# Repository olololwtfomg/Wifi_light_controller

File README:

Wireless sensor nodes used for simple communication protocol testing

Hardware:
RFM70 communication module
ATmega8L
DS18B20 one wire temperature sensor (for the hell of it)
generic 3.3-2.7V low drop voltage regulator

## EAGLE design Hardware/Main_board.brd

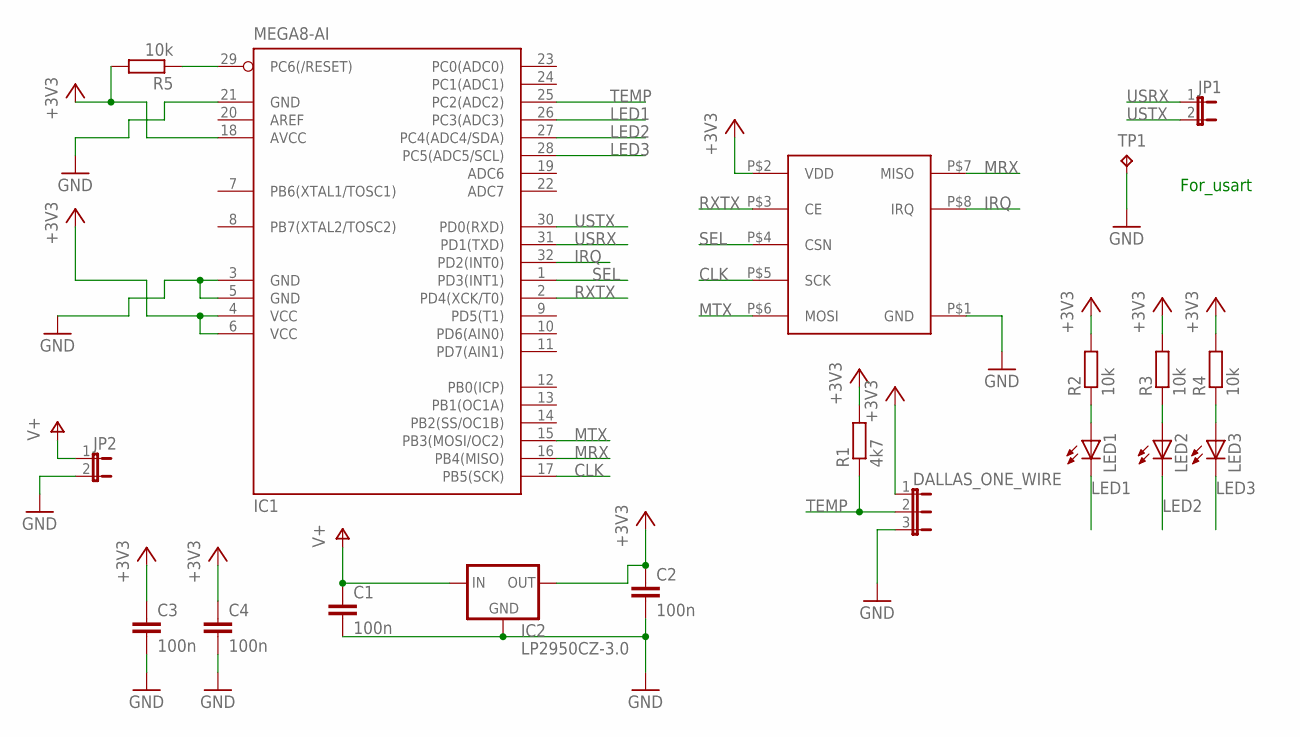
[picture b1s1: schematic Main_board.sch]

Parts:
C1, C2, C3, C4: 100n; C1206
DALLAS_ONE_WIRE: JP2E; JP2
IC1: MEGA8-AI; TQFP32-08
IC2: LP2950CZ-3.0; TO92
JP1, JP2: JP1E; JP1
LED1, LED2, LED3: LEDSMT1206; 1206
R1: 4k7; M1206
R2, R3, R4, R5: 10k; M1206
TP1: TPB2,54; B2,54
U$1: RFM70D

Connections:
+3V3: C2.1, C3.1, C4.1, DALLAS_ONE_WIRE.1, IC1.4 (VCC), IC1.6 (VCC), IC1.18 (AVCC), IC2.1 (OUT), R1.2, R2.2, R3.2, R4.2, R5.2, U$1.P$2 (VDD)
CLK: IC1.17 (PB5(SCK)), U$1.P$5 (SCK)
GND: C1.2, C2.2, C3.2, C4.2, DALLAS_ONE_WIRE.3, IC1.3 (GND), IC1.5 (GND), IC1.21 (GND), IC2.2 (GND), JP2.2, TP1.TP, U$1.P$1 (GND)
IRQ: IC1.32 (PD2(INT0)), U$1.P$8 (IRQ)
LED1: IC1.26 (PC3(ADC3)), LED1.C
LED2: IC1.27 (PC4(ADC4/SDA)), LED2.C
LED3: IC1.28 (PC5(ADC5/SCL)), LED3.C
MRX: IC1.16 (PB4(MISO)), U$1.P$7 (MISO)
MTX: IC1.15 (PB3(MOSI/OC2)), U$1.P$6 (MOSI)
unnamed: LED1.A, R2.1
unnamed: LED2.A, R3.1
unnamed: LED3.A, R4.1
unnamed: IC1.29 (PC6(/RESET)), R5.1
RXTX: IC1.2 (PD4(XCK/T0)), U$1.P$3 (CE)
SEL: IC1.1 (PD3(INT1)), U$1.P$4 (CSN)
TEMP: DALLAS_ONE_WIRE.2, IC1.25 (PC2(ADC2)), R1.1
USRX: IC1.31 (PD1(TXD)), JP1.1
USTX: IC1.30 (PD0(RXD)), JP1.2
V+: C1.1, IC2.3 (IN), JP2.1

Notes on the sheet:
For_usart

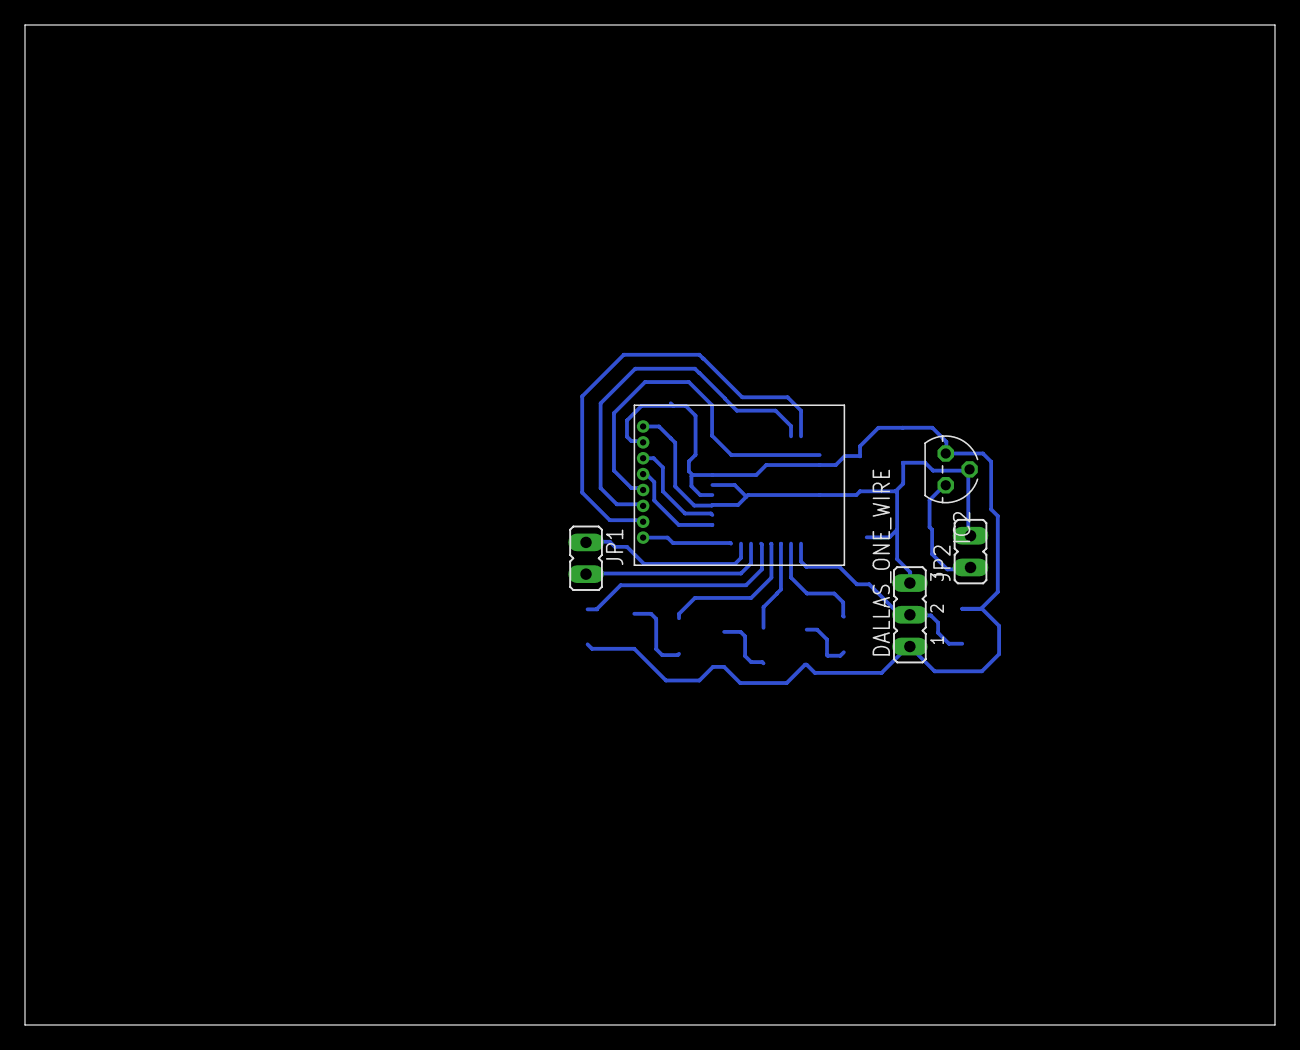
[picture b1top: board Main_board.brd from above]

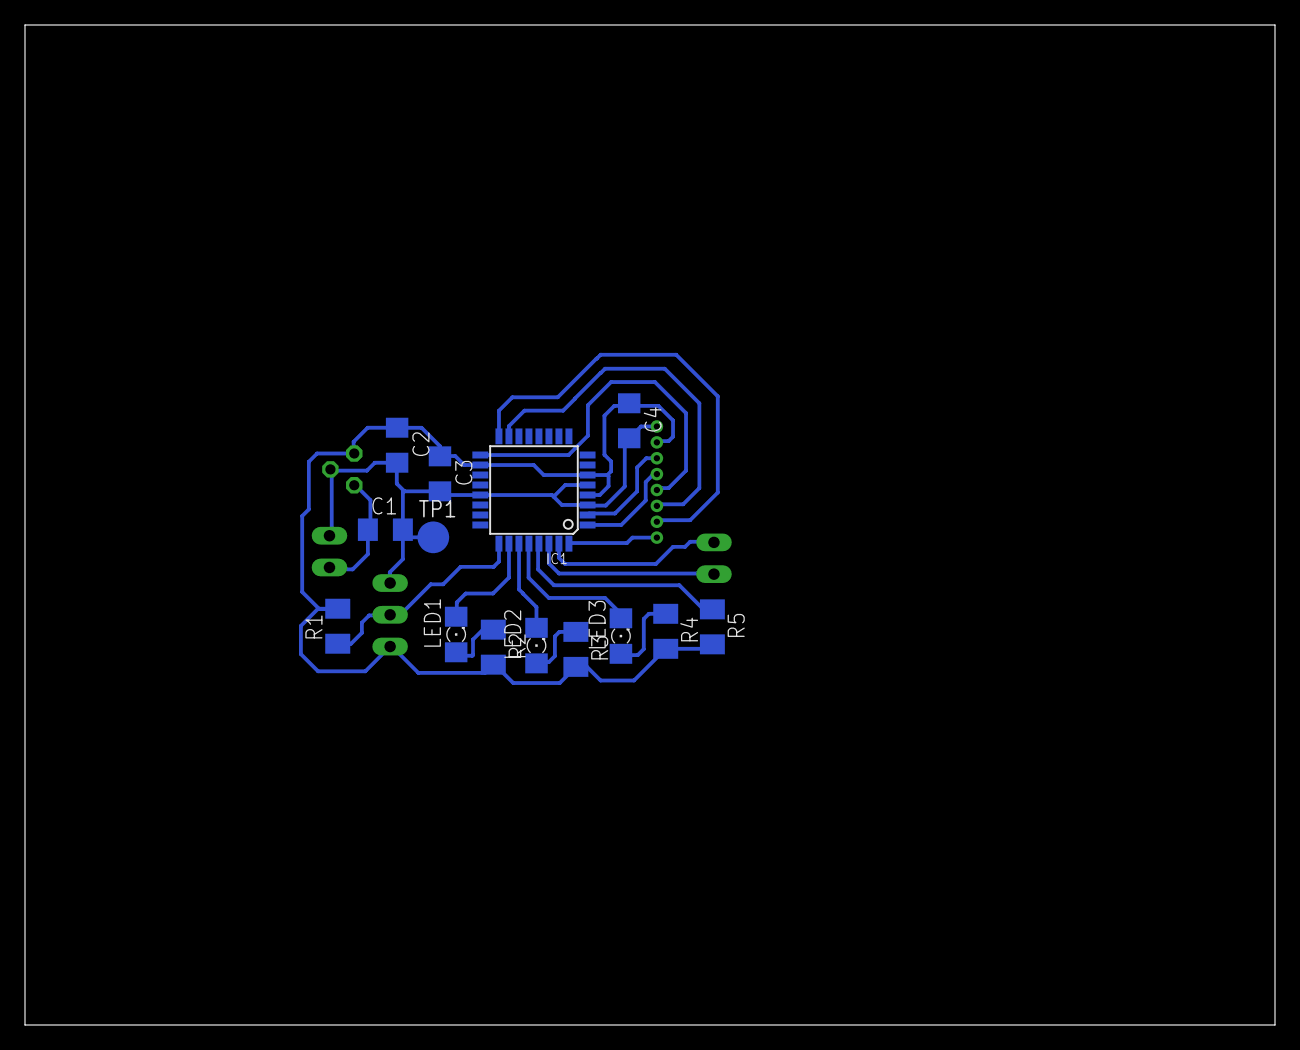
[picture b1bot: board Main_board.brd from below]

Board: 2 copper layers, 100.0 x 80.0 mm, 19 parts (14 on the bottom side), 19 nets.

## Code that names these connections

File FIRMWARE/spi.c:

#include <avr/io.h>
#include <inttypes.h>

#include "spi.h"
#include "bitops.h"

void SPI_MasterInit(void)
{
   //SPCR = 0b01010001;
#if SPI_INTERRUPT_ENABLED==1
   SPCR = (1<<SPIE)|(1<<SPE)|(1<<MSTR);
#else
    SPCR = (1<<SPE)|(1<<MSTR);
#endif
   SPSR = (1<<SPI2X); //DOUBLE SPEED WOOHOO
}

/*
*/
char SPI_RW(uint8_t sentByte)
{
    SPDR = sentByte;
#if SPI_INTERRUPT_ENABLED==0
    char retByte;
    while(!(SPSR&(1<<SPIF)));
    retByte=SPDR;
    return retByte;
#else

#endif
}

void RFM70_CSN(uint8_t state)
{
    if(state==0)
        BitClr(PORTD,(1<<PD3));
    else
        BitSet(PORTD,(1<<PD3));
}

void RFM70_CE(uint8_t state)
{
    if(state==0)
        BitClr(PORTD,(1<<PD4));
    else
        BitSet(PORTD,(1<<PD4));
}

void RFM70_MOSI(uint8_t state)
{
    if(state==0)
        BitClr(PORTB,(1<<PB3));
    else
        BitSet(PORTB,(1<<PB3));
}

void RFM70_SCK(uint8_t state)
{
    if(state==0)
        BitClr(PORTB,(1<<PB5));
    else
        BitSet(PORTB,(1<<PB5));
}

/*
void SPI_MasterTransmit(char cData)
{

   PORTB = 0b00000000;
     SPDR = cData;
     while(SPSR == 0b00000000);
   PORTB = 0b00000100;

}
*/

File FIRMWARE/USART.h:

/*
 to be honest this file includes physical debugging methods like LEDs and others
*/

#ifndef USART_H_INCLUDED
#define USART_H_INCLUDED

#include <avr/io.h>
#include <inttypes.h>

#define FOSC 1000000
#define BAUD_RATE 4800
#define UBBR_VALUE FOSC/16/BAUD_RATE-1

typedef enum
{
    LED1=PINC3,
    LED2=PINC4,
    LED3=PINC5
} eLeds;

typedef enum
{
    OFF,
    ON,
    TOGGLE
} eLedAction;
void USART_init(uint16_t ubrr);
void debug_send(char* str);
void LED_action(uint8_t led,uint8_t action);

#endif // USART_H_INCLUDED

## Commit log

2012-06-14 first hardware design
2012-06-18 started work on firmware
2012-06-22 Working USART
2012-06-28 Firmware with working utilities
